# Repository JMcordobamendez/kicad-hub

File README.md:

# kicad-hub

Git-based hardware design review for KiCad, running entirely on GitHub.

The goal is the collaboration experience of commercial PCB cloud platforms
(design checks, BOM review, release packages, web viewer, visual diffs) for KiCad
projects, using only free and open-source tools on top of plain git, GitHub Actions
and GitHub Pages. No extra server to maintain.

kicad-hub is an independent project, not affiliated with or endorsed by the KiCad
project. KiCad is a trademark of its respective owners.

> **Status:** v1.3 — CI checks, BOM review, suppliers, fab package, variants and the
> design portal (compare, comments, nets, cross-probing) work and are tested on every push with a real
> board (see [what works today](#what-works-today)). Next steps: the
> [roadmap](docs/ROADMAP.md).

New here? Read the [manual](docs/manual.md).

| Changed sheet, swipe between before and after | The report posted on the pull request |
|---|---|
|  |  |

More: [schematic](docs/screenshots/portal-schematic.png) ·
[BOM](docs/screenshots/portal-bom.png). Real screenshots of the example board's
portal and PR comment, taken by the "Docs screenshots" workflow.

## What works today

On every push and pull request of a KiCad project, the action:

- **Checks the design**: ERC and DRC (plus schematic/PCB parity) with `kicad-cli`.
  Non-blocking by default; `strict: true` fails the job on errors.
- **Checks the BOM**: every fitted part needs the required fields (by default
  footprint, datasheet and MPN or LCSC code); capacitors need a voltage rating.
- **Checks your requirements**: a `kicad-hub-requirements.yaml` next to the project
  (cost per board, layers, board size, stock, parts...) is checked on every run and
  shown as a pass/fail table; `strict: true` fails the job on a failed requirement.
- **Diffs the BOM** of a pull request against its target branch: parts added,
  removed and changed (`Value: 10uF → 22uF`).
- **Resolves the datasheets**: links checked (broken vs. not checked: a slow or bot-blocking site gets one retry
  and is then listed apart, never as broken), local PDFs
  found by MPN or value in the datasheet folders and bundled for offline use.
- **Prices the BOM from several suppliers**: price and stock of every part at LCSC
  and JLCPCB (no API key needed) and at Mouser, Farnell and DigiKey (with your own
  free API keys); cost per board and per batch (1, 5, 10, 100 boards) for every
  variant; a page to compare offers part by part and choose the supplier, saved in
  the repo. Warns on parts out of stock, not active, not found, or whose LCSC code
  doesn't match the MPN.
- **Builds a fab package** in standard formats any fab house accepts (Gerber X2,
  Excellon, IPC-D-356, BOM and pick & place CSV) with fab notes read from the
  board, which warn about features below the project rules.
- **Reports** all of the above in the job summary and as **one comment on the PR**,
  updated on every push.
- **Builds every design variant** (KiCad 10 variants, read from the project): the
  report lists what each one fits, leaves out or changes, warns when a variant
  changes a value but keeps the part number, diffs each variant in pull requests,
  and the fab package gets a BOM and pick & place per variant. Pick & place follows the
  schematic's per-variant DNP, so the report also compares the schematic with the PCB
  (DNP, excluded-from-BOM / position-files attributes, references, values, and the
  PCB's own per-variant overrides when the board stores them) and shows a "Schematic vs
  PCB" line per build: "in sync" or a table to fix with *Update PCB from Schematic*. The
  fab notes warn when a build's pick & place disagrees with the PCB.
- **Shows before/after images** of the schematic sheets and PCB layers changed in a
  pull request, right in the PR comment: removed in red, added in green, each
  changed area boxed.
- **Publishes a design portal** on GitHub Pages: one page per branch, release and
  pull request with the schematic and PCB in the browser
  ([KiCanvas](https://kicanvas.org)), the report, interactive BOM, supplier
  comparison, datasheets and downloads; the PR comment links to it. Keeps a **timeline**
  of the last commits of `main` and the releases, a page to **compare any two
  versions** (BOM, schematic sheets, PCB layers) and an **activity** page with the
  branch graph, pull requests, reviews, comments and pushes.
- **Publishes a GitHub Release** with the fab package when you tag `vX.Y`.
- Also: schematic PDF, BOM (CSV/HTML) and interactive BOM.

A board still being drawn (no outline on `Edge.Cuts`) skips DRC and the PCB outputs
with a warning instead of failing.

## Planned

Details and progress: [roadmap](docs/ROADMAP.md).

## How the pieces fit together

```
 KiCad (each designer)
        │  git push / pull request / tag
        ▼
 GitHub repository ──► GitHub Actions ── kicad-hub action (Docker: KiCad 10 + KiBot)
                          │
                          ├─ kicad-cli ── ERC / DRC
                          │            ── per-part BOM (this commit + PR base)
                          │            ── SVG of every sheet/layer (this commit + PR base)
                          │            ── fab package: Gerber X2, Excellon,
                          │               IPC-D-356, BOM, pick & place
                          ├─ Python ──── scripts/datasheets.py  resolve, check, bundle
                          │            ── scripts/fabnotes.py    fab notes from the board
                          │            ── scripts/sourcing.py    cost and stock (LCSC, JLCPCB,
                          │                                      Mouser, Farnell, DigiKey)
                          │            ── scripts/visual_diff.py before/after images
                          │            ── scripts/renders.py     page renders for the compare page
                          │            ── scripts/activity.py    branches, PRs, pushes for the activity page
                          │            ── scripts/report.py      markdown report
                          ├─ KiBot ───── schematic PDF, BOM CSV/HTML, iBOM
                          │
                          ├──► job summary + sticky PR comment (images: branch kicad-hub-images)
                          ├──► design portal (branch kicad-hub-site → GitHub Pages)
                          ├──► artifact <board>-fab
                          └──► GitHub Release (on tags)

 GitHub Pages (branch kicad-hub-site): design portal, one page per branch / release / PR
```

`kicad-cli` is used wherever possible: it respects the settings saved in the
project (plot layers, rules) and its options are stable. KiBot is kept for the
outputs it does best.

## Usage

kicad-hub is a GitHub Action. A board repository only needs a small workflow:

```yaml
# .github/workflows/kicad.yml in your board repository
name: KiCad

on:
  push:
    branches: [main]
    tags: ["v*"]         # tagging vX.Y publishes the fab package as a release
  pull_request:

permissions:
  contents: write        # releases and PR images (read = neither)
  pull-requests: write   # PR comment with the report
  issues: read           # issues on the activity page (needed in private repositories)

jobs:
  board:
    runs-on: ubuntu-latest
    steps:
      - uses: actions/checkout@v4
        with:
          lfs: true
      - uses: JMcordobamendez/kicad-hub@v1
        with:
          project-dir: hardware/my-board   # folder with the .kicad_pro
```

Ready-made workflows are in [`template/.github/workflows/`](template/.github/workflows/):
`kicad.yml` (the one above, with every option and the supplier keys) and
`kicad-hub-cleanup.yml`, which removes a pull request's before/after images and its
portal page when it is closed (or by hand, *Run workflow* with a PR number). Copy both to `.github/workflows/` in your board repository.

**Versions:** `@v1` always points to the latest 1.x release (no breaking changes);
pin a full tag such as `@v1.0.0` to freeze it, or use `@main` for the development
version.

### Inputs

| Input | Default | What it does |
|---|---|---|
| `project-dir` | — | Folder with the `.kicad_pro` (required) |
| `strict` | `false` | Fail on ERC/DRC errors or a failed requirement |
| `required-fields` | `Footprint,Datasheet,MPN\|LCSC` | Fields every fitted part needs; `A\|B` = either |
| `check-capacitor-voltage` | `true` | Capacitors need a `Voltage` field or a value like `10uF 16V` |
| `datasheet-dirs` | — | Extra folders with datasheet files (matched by MPN or value) |
| `datasheet-optional-refs` | `R,C,TP,H,MH,FID,JP,NT,LOGO` | Prefixes that don't need a datasheet |
| `check-datasheet-links` | `true` | Check that datasheet URLs respond |
| `variants` | `auto` | Design variants to build: `auto` (all in the project), a list, or `none` |
| `sourcing` | `true` | Price and stock per supplier, and the comparison page |
| `boards` | `1,5,10,100` | Batch sizes to price (components only) |
| `currency` | `USD` | Currency for all prices (converted with ECB rates) |
| `sourcing-choices` | `kicad-hub-sourcing.csv` | Supplier picked per part, relative to `project-dir` (see [choosing suppliers](#choosing-suppliers)) |
| `mouser-api-key` | — | Mouser Search API key, from a secret ([how](#supplier-api-keys)) |
| `farnell-api-key` | — | Farnell / element14 API key, from a secret |
| `farnell-store` | `uk.farnell.com` | Farnell store to price from (`es.farnell.com`, `de.farnell.com`, `www.newark.com`…) |
| `digikey-client-id` | — | DigiKey API client ID, from a secret |
| `digikey-client-secret` | — | DigiKey API client secret, from a secret |
| `requirements` | `kicad-hub-requirements.yaml` | Requirements file, relative to `project-dir` (see [requirements](#requirements)); no file = nothing checked |
| `pages` | `true` | Publish the design portal (see [design portal](#design-portal)) |
| `pages-branch` | `kicad-hub-site` | Branch the portal is published to |
| `history` | `10` | Light snapshots of the last N commits of the default branch for the portal's timeline and compare page; `0` = off |
| `pr-commits` | `20` | Light snapshot of the head commit of every push to a pull request (`/pr-<N>/commits/<sha7>/`), the newest N per PR, to compare a PR's commits with each other; `0` = off |
| `activity` | `500` | Activity page of the portal: graph of the last N commits of all branches, pull requests, reviews, comments, releases and pushes (see [activity](#activity)); `0` = off |
| `visual-diff` | `true` | On PRs, before/after images of the changed sheets and layers in the comment (stored in the `kicad-hub-images` branch) |
| `fab-profile` | `generic` | Optional fab layer: `jlcpcb`, `pcbway` or `eurocircuits` (see [fab profiles](#fab-profiles)) |
| `extra-formats` | — | Extra formats in the fab package: `odb`, `ipc2581` |
| `release` | `true` | On tags, attach the fab package to a GitHub Release |
| `comment` | `true` | Post the report on the PR |
| `github-token` | `github.token` | Token for the PR comment and the release |
| `image` | `ghcr.io/inti-cmnb/kicad10_auto:1.9.1` | Docker image with KiCad and KiBot |
| `output-dir` | `fab` | Where outputs are written |

Outputs: `has-pcb`, `missing-fields`, `requirements-failed`.

Datasheet folders searched by default: `datasheet(s)/` and `docs/` next to the
project, and `datasheet(s)/` one level up. A file is used when its name contains
the part's MPN or value, or its family code (`S-82A2A_B_C.pdf` →
`S-82A2AAA-A8T2U`).

### Fab profiles

The package and the checks are generic by default. `fab-profile` adds an optional
layer for one fab, without changing the project's own DRC or `strict`:

- **DRC vs the fab's rules**: a second DRC on a copy of the project, with the fab's
  published capabilities (`fab-profiles/<name>/rules.kicad_dru`) appended to the
  project's own `.kicad_dru`. Shown as its own line in the report, the PR comment and
  the portal; the artifact has `reports/drc-fab.rpt|json`. It never fails the build.
- **Assembly files** in the fab's column layout, next to the generic ones
  (`assembly/jlcpcb/`: BOM `Comment, Designator, Footprint, LCSC Part #` from the
  `LCSC` field, and CPL `Designator, Mid X, Mid Y, Layer, Rotation`).
- A note in the package's `README.txt`.

| Profile | Rules | Assembly files |
|---|---|---|
| `jlcpcb` | standard 2-layer/multilayer, 1 oz | yes |
| `pcbway` | standard process, 1 oz | no (generic files) |
| `eurocircuits` | only limits independent of the pattern class | no (generic files) |

Each `rules.kicad_dru` cites its source page and date. KiCad rules can't test the
layer count, so where 2-layer and multilayer limits differ the safer value is used.

### Design portal

Every push to a branch, tag and pull request publishes a page to the
`kicad-hub-site` branch, served by GitHub Pages at
`https://<owner>.github.io/<repo>/`:

- `/<branch>/` (e.g. `/main/`), `/releases/<tag>/`, `/pr-<N>/`, and a front page
  listing them all;
- each page has tabs: **Schematic** (sheet picker) and **PCB** (top/bottom, layer
  list with presets), both with pan, zoom and a side panel that shows the clicked
  part (value, footprint, nets, datasheet, best supplier offers); on pull requests,
  **Changes vs <base>** (BOM changes, and each changed sheet or layer in an interactive
  compare: swipe, fade, side by side or red/green changes, with zoom and pan); then **Interactive
  BOM**, **BOM**, **Suppliers**, **Report**, **Datasheets** and **Downloads** (fab
  package, schematic PDF, BOM CSV, commit history);
- **nets in the schematic**: click a wire, bus, junction, label, power symbol or pin and its
  net is highlighted on the sheet (the rest dims) and on the other sheets it runs through,
  with a **Net in the schematic** card (Prev / Next sheet, **Show on PCB**). The viewer builds
  the schematic's connectivity itself (a [fork of KiCanvas](scripts/vendor/README.md));
- **cross-probing**: with a footprint selected, **Show in schematic** opens the sheet that
  has the symbol (a multi-unit part opens on its first unit) and selects it, and **Show on
  PCB** does the reverse (turning the board to the footprint's side); a highlighted net
  has **Show in schematic**, which highlights it sheet by sheet (Prev / Next sheet), and
  the nets of a selected symbol or of a picked wire highlight on the board. An optional
  **Sync** toggle (`?sync=1`) selects the part, or the net, in both tabs;
- a version picker in the top bar jumps between branches, the history of `main`,
  releases and PRs, and opens the timeline or the compare page;
- **History** (front page, `#history`): the last commits of `main` (input `history`,
  default 10, `0` = off) and the releases, newest first, with date, commit, message,
  author, ERC/DRC status, **Open**, **Compare with previous** and **Compare with…**.
  Each push to `main` adds a light snapshot at `/history/<short-sha>/` (design files if
  under 6 MB, page renders, parts BOM, commit info; no fab package, offers or PDFs) and
  the oldest beyond `history` are removed. Releases keep their full pages;
- **Compare** (`/compare.html`, or `compare.html?a=<path>&b=<path>` with paths such as
  `main/`, `history/<sha>/`, `releases/<tag>/`, `pr-3/`): pick any two versions. It shows
  the BOM changes (added, removed, changed fields) and every schematic sheet and PCB layer
  in the interactive compare (swipe, fade, side by side, or **Changes**: red only in A,
  green only in B), computed in the browser from full-page renders that every published
  build stores in `renders/` (same export options and resolution, no crop, so any two
  builds line up). Without parameters it opens on the newest version against the one before
  it (a PR's previous push, else the default branch; for `main` the previous snapshot). Pages identical in both are collapsed as "no changes". Builds
  published before this feature have no renders until their next publish.
- **Commits of a pull request**: every push to a PR also publishes a light snapshot of its
  head commit at `/pr-<N>/commits/<sha7>/` (same content as a `history/` snapshot; input
  `pr-commits`, default the newest 20 per PR, `0` = off; they go away with the PR's page). A PR
  page gets a **Commits** tab: its pushes as a strip (comments counted above each), click one
  for **A** and another for **B** and the two are compared right there (BOM changes and every
  sheet and layer), with a link to the full compare page. The snapshot is the PR merged into its base
  at that push, like the `/pr-<N>/` page, and only the head commit of each push gets one (a push
  of three commits makes one snapshot); a PR pushed before the feature has none until its next push;
- **Activity** (`/activity.html`, linked from the front page and the top bar): how the
  work evolved, with commits, pull requests, comments and issues in one graph, see [below](#activity);
- **Nets and measuring** in the viewer: on the PCB tab, the **Nets** card searches every
  net of the board as you type; the nets of the selected part are buttons too, and a click on
  a track does the same. The net's tracks, vias, pads and zones are highlighted and the
  copper dimmed, with its pad, track (length), via and zone count; **Prev / Next pad**
  centres each pad in turn ("U3 pad 12 · 3 of 18", turning the board over for a pad on the
  other side). **Measure** (PCB and schematic) draws the distance, dx and dy between two
  clicks or taps (on the PCB the points snap to a pad centre when you click near one).
  **Esc** or **Clear** drops the highlight and the measurement. Measure and **Comment** are
  exclusive. The schematic has no net highlight (the viewer doesn't offer one);
- **Design variants** in the viewer: when the design has KiCad variants, the Schematic and
  PCB toolbars get a **Variant** picker (default | each variant), the same in both tabs and
  kept in the URL (`?variant=lite`, so a link opens that variant). The parts not fitted are
  marked: on the PCB a hatched box with a red X and a "DNP" label over each footprint
  (the other side of the board as a faint outline), on the schematic KiCad's own DNP cross
  over the symbol. The toolbar says how many parts the variant leaves out and changes, and
  the **Selected** card shows that variant's values (`C10: 10uF (default: 100nF)`), "Not
  fitted in lite" for a part left out, and its own offers if the variant orders another part;
- on pull request pages, **comments pinned on the board** (see below).

The viewer is a pinned copy of KiCanvas (`scripts/vendor/`, see its README), not
loaded from a third-party site, so published pages don't change under you.

**Turn it on once:** after the first run, *Settings → Pages → Build and deployment →
Source: Deploy from a branch → `kicad-hub-site` / `(root)` → Save*. The PR comment
links to the PR's page. The branch keeps a single commit, replaced on every
publish, so it doesn't grow; the cleanup workflow removes a PR's page when it is
closed. Pull requests from forks aren't published (they can't write to the repo).

**No Pages, no link.** The action asks the GitHub API whether Pages serves the portal
branch. If not (typically a private repository without a paid plan, or Pages not enabled
yet) the PR comment and job summary say so instead of linking to a 404; the portal branch
is still published, so it works as soon as Pages is turned on. If the token can't read the
setting the link is kept as before.

#### Activity

`activity.html` draws the history of the repository: a lane graph of the last commits of
every branch and tag (newest on top, one colour per lane, merge curves, a star on
releases) with what happened between them on the same timeline: pull requests opened,
merged or closed, reviews and review comments, pinned board comments and conversation
comments, issues opened, commented and closed, releases. Next to each commit: subject,
author, date, sha and a green *snapshot* mark when the portal has a page of that exact
commit. A chip at each branch tip shows who created the branch: the author of its pull
request, else of its first commit, else whoever pushed it first. Hover (or focus) an event
to highlight its commits and the reverse. **Show** checkboxes (main, pull requests, PR
commits, comments, issues, releases) and filters (branch, author, dates) narrow it down.

- **Pick two commits to compare**: click a commit (its row or its node) and it becomes **A**,
  click another and it becomes **B**; a third click starts again, and clicking A or B lets it
  go. The bar above the graph shows both, with **Compare A ↔ B** (opens `compare.html` with
  them) and **Clear**. From the keyboard: arrows move between rows, Enter picks, `a` / `b` set
  that slot. Commits without a snapshot are greyed, with a tooltip saying why (only the last
  commits of `main`, the head of each PR push and releases are published): they can still be
  selected to read, not compared. Works for `main`, PR commits and releases alike. A and B are
  kept in the URL (`?a=<sha7>&b=<sha7>`).
- **Side panel** for the selected commit: message, author, date and branch; its pull request
  (title, description, number of commits and snapshots, ERC/DRC of the PR build); the PR's
  review comments (marked *on this commit* when GitHub knows the commit), pinned board comments
  (linking back to the part) and conversation; and the related issues (referenced as `#12`,
  `closes #12` or a link in a commit message or a PR title or description) with their
  description and every comment. Descriptions and comments are GitHub Markdown, sanitised with
  the portal's DOMPurify; pictures are shown as links. **Open this version**, **Set as A / B**,
  **Compare with parent** and **View on GitHub** are at the bottom.
- **Data**: git (all branches and tags in topological order; a shallow checkout is
  deepened and all branches are fetched, so the graph is complete without
  `fetch-depth: 0`) and the GitHub GraphQL API with the action's `github-token` (the last
  100 pull requests with reviews, review comments and comments, the releases, and up to 40
  issues the commits and PRs mention, one query per ten: well inside the rate limit, and skipped
  when little is left). The page itself (`activity.json`) stays light: texts of the selected commit
  are in `activity-details.json`, fetched on the first click (capped at about 2.5 MB: long
  texts are cut). In a **private** repository the token needs `issues: read` (add it to the
  workflow's `permissions`); without it the page says the issues are missing and shows the rest.
  Without the token or when GitHub doesn't answer, the page shows the git graph alone.
- **Pushes**: GitHub doesn't keep who pushed a branch, so every run of a push (and every
  update of a pull request's branch) appends `{actor, ref, before, after, date}` to
  `activity-pushes.json` in the site branch (the last 1000). Pushes made before the first
  run with this feature are not known; the page says since when it records.
- **Privacy**: no e-mail address is ever published. Authors are shown by GitHub login (and
  avatar from `avatars.githubusercontent.com`) when known, else by the name in the commit,
  and anything that looks like an address is removed from commit messages and comments
  (`Co-authored-by` and `Signed-off-by` lines are dropped). Issue and PR texts are published
  to the repository's own Pages site, so they are as public as that site.
- Input `activity` sets how many commits to read (default 500, `0` = no page). Pull requests
  from forks aren't published, so they never reach it.

#### Comments on the board

On a pull request's page, the **PCB** and **Schematic** tabs have a **Comment** button.
Press it, click a part or any point of the board (or type the coordinates), write the
note and post it: it becomes a normal comment in the pull request's conversation,

```
📍 **U12** (x 23.40, y 41.10 mm, F.Cu) — missing decoupling

[Open on the board](https://<owner>.github.io/<repo>/pr-7/?at=23.4,41.1&ref=U12#pcb)
<!-- kicad-hub-pin {"ref":"U12","x":23.4,"y":41.1,"layer":"F.Cu","page":"pcb","sha":"…"} -->
```

with a hidden marker that the portal reads back. The **Comments** card in the side
panel lists the pins of that tab (author, part, text, link to the GitHub comment);
click one to select and zoom to the part (or the point), and numbered markers are
drawn over the viewer and follow pan and zoom. The link in the comment opens the page
on that spot. Anyone can also write such a comment by hand: the marker is all it needs.
Branch and release pages don't show comments.

Reading the pins needs nothing (public repositories, 60 anonymous requests per hour).
**Posting** from the page needs a token; without one, **Comment** copies the formatted
comment to the clipboard and opens the pull request, where you paste it.

*Make the token once* (GitHub, in the browser):

1. Click your profile photo, top right → **Settings**.
2. Left sidebar, at the bottom → **Developer settings**.
3. **Personal access tokens** → **Fine-grained tokens** → **Generate new token**.
4. **Token name**: `kicad-hub comments`. **Expiration**: 30 days is plenty.
5. **Resource owner**: the owner of the board repository (an organization may need to
   allow fine-grained tokens, or approve the request).
6. **Repository access** → **Only select repositories** → pick the board repository.
7. **Permissions** → **Repository permissions** → **Pull requests** → *Access:*
   **Read and write** (Metadata: Read-only is added by itself). Nothing else.
8. **Generate token**, copy it (`github_pat_…`) and paste it in the **GitHub token**
   box at the bottom of the Comments card → **Save**.

The token is kept in this browser's `localStorage` and sent only to `api.github.com`,
never in a URL or to any other site. **Forget token** (same box) removes it. Comments
are posted under your GitHub account. `localStorage` is shared by every page under
`<owner>.github.io`, so keep the expiry short and the permission to that one
repository.

### Supplier API keys

LCSC and JLCPCB work out of the box: parts are looked up by their `LCSC` field
(e.g. `C25744`), no account needed. Mouser, Farnell and DigiKey need an API key,
which each user gets for free with their own account — kicad-hub has no shared
keys. Parts are looked up there by their `MPN` field, or by the manufacturer part
number LCSC reports when the MPN is empty. Add only the suppliers you want; the
others are skipped and listed as "no API key" in the report.

**1. Get the keys**

- **Mouser** — sign in at [mouser.com](https://www.mouser.com) (create an account if
  needed), open the [API Hub](https://www.mouser.com/api-hub/) and sign up for the
  **Search API**. The key is shown under *My Account → APIs* and sent by email.
  Limits: 30 requests per minute, 1,000 per day (one request per part).
- **Farnell / element14** — register at
  [partner.element14.com](https://partner.element14.com/), then *Register an
  application* / *Get API Keys* for the **Product Search API (REST)**. Copy the key.
  Pick your store with `farnell-store` (prices come in that store's currency).
- **DigiKey** — sign in at [developer.digikey.com](https://developer.digikey.com/)
  with a DigiKey account, create an organization, then a **Production App** with
  the **ProductInformation V4** API enabled (the OAuth callback can be
  `https://localhost`, it isn't used). Copy its **Client ID** and **Client Secret**.

**2. Store them as secrets of your board repository** (never in a file): *Settings →
Secrets and variables → Actions → New repository secret*, one per value:

| Secret name | Value |
|---|---|
| `MOUSER_API_KEY` | Mouser Search API key |
| `FARNELL_API_KEY` | element14 API key |
| `DIGIKEY_CLIENT_ID` | DigiKey Client ID |
| `DIGIKEY_CLIENT_SECRET` | DigiKey Client Secret |

**3. Pass them to the action** in your workflow:

```yaml
      - uses: JMcordobamendez/kicad-hub@v1
        with:
          project-dir: hardware/my-board
          currency: EUR
          mouser-api-key: ${{ secrets.MOUSER_API_KEY }}
          farnell-api-key: ${{ secrets.FARNELL_API_KEY }}
          farnell-store: es.farnell.com
          digikey-client-id: ${{ secrets.DIGIKEY_CLIENT_ID }}
          digikey-client-secret: ${{ secrets.DIGIKEY_CLIENT_SECRET }}
```

A secret that isn't set arrives empty and that supplier is skipped, so the same
workflow works with any subset. GitHub masks secrets in the logs. Pull requests
from forks don't get secrets: they are priced with LCSC and JLCPCB only.

### Choosing suppliers

By default each part is bought from the cheapest supplier that has enough stock for
the batch. To choose yourself:

1. Download the artifact of a run and open **`sourcing.html`**: one row per part,
   with every supplier's stock, minimum order, unit price and line total for the
   batch you select, and totals per build and batch.
2. Pick an offer per part (or *Use the cheapest for every part* to freeze the
   current choice). **Download purchase list** gives one CSV per batch, sorted by
   supplier, ready to paste into each supplier's cart.
3. **Download selection file** and commit it as `kicad-hub-sourcing.csv` next to
   the `.kicad_pro`. From then on the report's totals use your picks; parts not in
   the file stay automatic. It's a plain CSV (`Part,Supplier,SKU`, where `Part` is
   the MPN or the LCSC code), so it can also be edited by hand and reviewed in PRs.

**Target price.** An optional fourth column, `Target`, is the unit price you want to
pay for a part, in the `currency` input (`Part,Supplier,SKU,Target`). A row may carry
only `Part` and `Target`, leaving `Supplier` and `SKU` empty: no choice, just a
target. Files without the column keep working. In `sourcing.html` type the target
next to a part; offers above it turn red, and **Download selection file** writes
the column. The report's *Cost and stock* section then lists an **Above target
price** table (part, references, target, unit price of the offer used at the
largest batch, supplier, percentage over) and `above_target` is added to the
counts; `reports/sourcing.csv` has a `Target` column and a `Vs target @n` column per
batch, and `sourcing.json` a `vs_target` entry per part (`above`, `ok` or `no offer`).
The example board has a [`kicad-hub-sourcing.csv`](examples/royalblue54l-feather/kicad-hub-sourcing.csv)
with a few targets, one of them set too low on purpose so the warning shows.
A `Target price` symbol field is not read: the BOM export only carries the fields
listed in `required-fields`-style columns, so targets live in the CSV.

### Requirements

Write down what the board has to meet and let CI check it. Put a
`kicad-hub-requirements.yaml` next to the `.kicad_pro` (the `requirements` input
renames it); without the file nothing is checked and nothing is shown. Each entry
has an `id`, a human `text`, a `check` type and that check's parameters:

```yaml
- id: R1
  text: Cost per board under 15 EUR at 100 units
  check: max_cost
  batch: 100
  max: 15
```

The report gets a **Requirements** table (id, requirement, result, measured value) and
the portal's Checks panel counts the failed ones. A requirement is **pass**, **fail**,
or **unknown** when the data to check it isn't there (no prices, no board outline, a
batch that isn't priced): unknown never fails the job. A malformed entry (unknown check,
missing or misspelled parameter, duplicate id, invalid regex) is reported as **fail**
with the reason. Failed requirements fail the job only with `strict: true`. The file
is read with PyYAML inside the KiBot image; a top-level `requirements:` list is also
accepted. A commented template is in [`template/`](template/kicad-hub-requirements.yaml)
and a working one in [`examples/royalblue54l-feather/`](examples/royalblue54l-feather/kicad-hub-requirements.yaml).

| `check` | Parameters | Passes when |
|---|---|---|
| `erc_errors_max` | `max` (default 0), `severity` (`error`, or `warning`) | ERC violations of that severity ≤ `max` |
| `drc_errors_max` | `max` (default 0), `severity` | DRC violations ≤ `max` (unknown without a board outline) |
| `max_parts` | `max`, `variant` | Fitted parts (DNP excluded) ≤ `max` |
| `max_unique_parts` | `max`, `variant` | Distinct fitted parts ≤ `max` (same MPN or LCSC code, else same value and footprint, counts once) |
| `max_cost` | `max`, `batch`, `variant` | Components cost per board at `batch` boards ≤ `max`, in the `currency` input. `batch` must be in the `boards` input. Unknown if some parts have no price and the priced ones are still within `max` |
| `in_stock` | `batch`, `variant` | Every part has a supplier with stock for `batch` boards (the picked supplier if `kicad-hub-sourcing.csv` chooses one) |
| `max_above_target` | `max` (default 0), `batch` (default: largest in `boards`), `variant` | Parts whose used offer costs more than their `Target` in `kicad-hub-sourcing.csv` ≤ `max`. Unknown without any target |
| `no_bad_lifecycle` | `variant` | No part is obsolete / EOL / NRND at every supplier that reports its lifecycle |
| `max_layers` | `max` | Copper layers ≤ `max` |
| `max_board_size` | `width`, `height` (mm) | Board outline fits in `width` x `height`, either orientation |
| `min_track` | `min` (mm) | Narrowest track used ≥ `min` |
| `min_drill` | `min` (mm) | Smallest drill used (vias and plated pad holes) ≥ `min` |
| `required_fields` | `refs`, `fields`, `variant` | Every fitted part whose reference matches the regex `refs` (whole reference, e.g. `U\d+`) has all `fields` filled. Fields are the exported BOM columns (see `required-fields`) |
| `variants_in_sync` | `max` (default 0), `variant` | Differences between the schematic and the PCB (DNP, attributes, missing references, values) ≤ `max`, for every build or only `variant` |
| `forbidden_parts` | `pattern`, `variant` | No fitted part has an MPN or value matching the regex `pattern` (case-insensitive) |

`variant` is the name of a design variant; leave it out for the default build.
`max_cost`, `in_stock`, `max_above_target` and `no_bad_lifecycle` need `sourcing: true`.

### What you get

**Report** — job summary and PR comment:
ERC/DRC counts · requirements pass/fail · BOM changes vs. the PR base · before/after images · variants · parts missing required fields ·
datasheet status (broken links, offline copies) · cost per batch and stock warnings ·
fab package warnings.

**Artifact `<board>-fab`:**

```
reports/      erc/drc (.rpt, .json), per-part BOMs, report.md, datasheets.json,
              sourcing.csv (every supplier offer per part and batch)
sourcing.html supplier comparison: choose per part, download selection and purchase list
package/      <board>-<rev>-fab.zip  ← send this to the fab
  <board>-<rev>/
    gerber/       Gerber X2 + .gbrjob (layers as set in the board's plot settings)
    drill/        Excellon PTH and NPTH, drill maps (PDF)
    assembly/     BOM (CSV, grouped, no DNP) and pick & place (CSV, mm, both sides)
      <variant>/  the same for each design variant
      <fab>/      with a fab-profile: BOM and pick & place in that fab's columns
    *.d356        IPC-D-356 netlist for electrical test
    README.txt    fab notes: size, layers, stackup, finish, smallest features, warnings
    SHA256SUMS.txt
visual/       PRs only: before/after (<page>.png) and full-page overlay (<page>-full.png)
datasheets/   local datasheets + index.html (part → datasheet)
schematic/    schematic PDF
bom/          BOM CSV and HTML (KiBot)
ibom/         interactive BOM
```

The package revision is the tag on releases, else the title block revision, else
the commit hash.

## Repository layout

```
action.yml                  the action
fab-profiles/               optional per-fab DRC rules and assembly column layouts
scripts/                    fab_assembly.py, report.py, requirements.py, datasheets.py, fabnotes.py,
                            variant_cpl.py, variant_sync.py, visual_diff.py, renders.py (page renders for the
                            compare page), sourcing.py (+ sourcing.html, the comparison page),
                            portal.py (+ portal.html, the design portal; compare.html and
                            compare.js, the compare page and its shared widget;
                            pins.js, comments pinned on the board;
                            viewer-tools.js, nets and measuring;
                            variants-view.js, variant picker and DNP marks; activity.py +
                            activity.html, the activity page)
kibot/default.kibot.yaml    KiBot outputs (schematic PDF, BOMs, iBOM)
template/                   starting point for a new board repository
examples/                   boards used to test the action (see examples/README.md)
.github/workflows/test.yml  runs the action on the example board on every push/PR/tag
.github/workflows/kicad-hub-cleanup.yml  removes closed PRs' images and pages (same as the template's)
docs/                       roadmap and screenshots
```

New board repositories start from [`template/`](template/): folder layout,
`.gitignore`, `.gitattributes` (LF for KiCad files, Git LFS for 3D models),
project libraries through `${KIPRJMOD}`, a PR design review checklist and the CI
workflows.

### Approval flows

The template includes issue forms (part request, design review, fab release), a
`CODEOWNERS.example` and an opt-in approval step for releases, all plain GitHub
features. Step-by-step recipes: [`template/docs/approvals.md`](template/docs/approvals.md).

## Development

- Every push to `main`, every PR and every `v*` tag runs the action on
  `examples/royalblue54l-feather` (`.github/workflows/test.yml`). A PR shows the
  report comment. Version tags (`v*`) run the tests only; an `example-*` tag also
  publishes the example's fab package as a release, to test that step.
- The Python scripts can be run locally against files exported with a local
  `kicad-cli` (see the arguments at the top of each script). `fabnotes.py` needs
  KiCad's own Python (`pcbnew`); on Windows it may open a "font not found" dialog
  that blocks until closed — that doesn't happen in CI.

## Report notes

- **BOM changes** list the fields of a changed part by importance (Value, Footprint,
  MPN/Manufacturer, supplier codes, the rest). Datasheet URL changes are not in the row,
  only "datasheet link changed", with the before/after in a collapsed list.
- **Lifecycle** (obsolete, NRND, EOL…) is a status of one supplier's orderable part. It is a
  warning only when it hits an offer the totals use or several suppliers report it;
  otherwise it is a note in `sourcing.html`.
- If the workflow calls the action at a branch (`@main`) the report says it is a
  development branch; pin `@v1` for the stable version. No note for tags or commit SHAs.

## Known limits

- **No real-time co-editing.** KiCad files don't merge well: split work by
  hierarchical sheet and keep a single owner for the PCB at a time.
- **GitHub Pages is free only for public repositories** (private ones need a paid
  plan); without Pages the portal branch is still published but not served.
- The viewer is KiCanvas, still in alpha: some KiCad features may not display.
- PR commit snapshots are of the head commit of each push (not every commit of a push), are
  the PR merged into its base at that moment (so they include whatever the base had then), and
  cost the size of a light snapshot each: 20 per open PR is the default, lower `pr-commits` for
  big boards.
- Pinned comments are a prototype (phase 5): conversation comments only (no replies or
  resolving from the page, no review comments on the diff), a pin keeps the position
  where it was made even if the part moves in a later commit, and the viewer's clicks
  rely on KiCanvas internals. Only on pull request pages of github.com repositories.

## License

[MIT](LICENSE). The example board keeps its own license (CERN-OHL-P, see
[examples/README.md](examples/README.md)).

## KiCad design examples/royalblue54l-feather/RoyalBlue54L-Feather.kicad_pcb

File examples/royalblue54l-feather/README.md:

# RoyalBlue54L Feather

An ARM + RISC-V Feather board with the new nRF54L15, built-in debugger, and smart PMIC

## Overview

The RoyalBlue54L--familiar Feather formfactor with distinctive features. Nordic's next-gen nRF54L15, an onboard CMSIS-DAP debugger + UART bridge, and smart power-management features from the nPM1300 enable rapid development for your next Bluetooth 6.0, Thread, Matter, Zigbee, Amazon Sidewalk, or proprietary wireless project.

Crowd Supply project link: https://www.crowdsupply.com/lords-boards/royalblue54l-feather

## Hardware Features

* Dual-core processing power:
  * ARM Cortex-M33 at 128MHz
  * RISC-V co-processor at 128MHz
* Comprehensive memory configuration:
  * 1.5MB of non-volatile memory (NVM)
  * 256KB of RAM
  * 2MB external flash
* Advanced wireless capabilities:
  * BLE 6.0 support with channel sounding for distance estimation
  * 4Mbps PHY for proprietary wireless protocols
  * 30-50% power reduction compared to nRF52 series
* Integrated development tools:
  * CMSIS-DAP debugger (nRF52833-based)
  * USB-to-UART bridge
  * Open source, Zephyr RTOS-based firmware
* Smart power management:
  * USB-C charging up to 800mA with nPM1300
  * High-accuracy battery fuel gauge
* Connectivity:
  * JST-PH connector
  * STEMMA-QT/Qwiic port
  * NFC antenna connector
* User interfaces:
  * User LED
  * RGB LED (nPM1300-driven)
  * User button
  * Reset button

## Project Contents

This project contains the hardware design files for the RoyalBlue54L Feather. The board is designed with KiCAD and includes:

* Schematic files
* PCB layout
* Bill of Materials (BOM)
* Documentation

## Related Repositories

* [Zephyr Board Support](https://github.com/LordsBoards/RoyalBlue-nRF54L15-Zephyr-Boards)
* [Debugger Firmware](https://github.com/LordsBoards/RoyalBlue-nRF54L15-Debugger-Firmware)

## License

Hardware files are released under CERN-OHL-V2-P.

## Modification Note

Modified by KiCad Project Feb 17, 2025
 - Removed Manufacturing files
 - Update README.md

## kicad-hub

`kicad-hub-sourcing.csv` sets target unit prices (USD) for four parts (`Part,Supplier,SKU,Target`, no supplier chosen). `C307331` has a target set far below its real price on purpose, so the report shows an "Above target price" table.

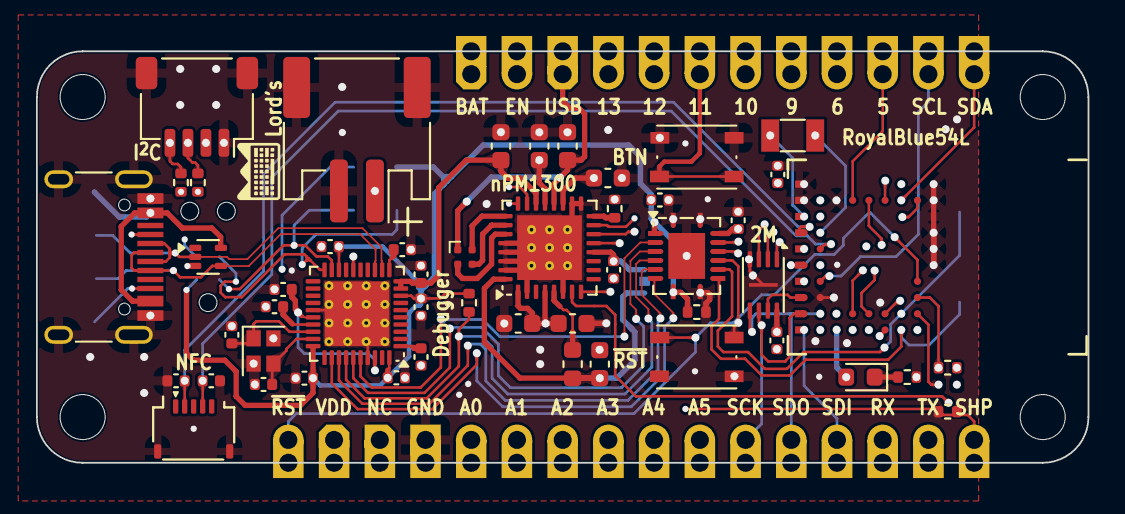
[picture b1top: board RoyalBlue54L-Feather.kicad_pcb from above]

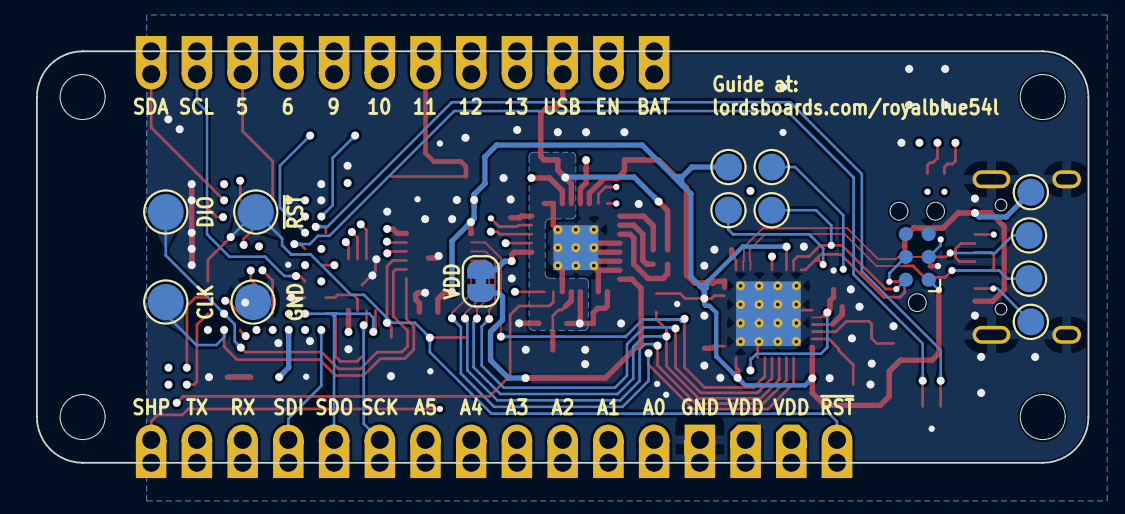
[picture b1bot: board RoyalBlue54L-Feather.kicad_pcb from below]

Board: 8 copper layers, 58.4 x 22.9 mm, 71 parts (15 on the bottom side), 68 nets.

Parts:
C1, C12, C16, C17, C19, C24, C25: 100nF; C_0402_1005Metric
C2, C3, C4, C8: 10uF; C_0603_1608Metric
C5, C6: 1uF; C_0603_1608Metric
C7, C9, C10, C23: 4.7uF; C_0402_1005Metric
C11: 2.2uF; C_0603_1608Metric
C13, C14: 300pF; C_0402_1005Metric
C15, C22: 1uF; C_0402_1005Metric
C18, C20: 12pF; C_0402_1005Metric
C21: 100pF; C_0402_1005Metric
D1: LED_Small; LED_0603_1608Metric
D3: LED_ARGB; LED_Wurth_150044M155260
H1, H2, H3, H4: MountingHole; MountingHole_2.5mm
J1: Conn_01x16_Pin; PinHeader_1x16_P2.54mm_Vertical
J2: Conn_01x12_Pin; PinHeader_1x12_P2.54mm_Vertical
J3: USB_C_Receptacle_USB2.0_16P; USB_C_Receptacle_HRO_TYPE-C-31-M-12
J4: Conn_01x02_MountingPin; JST_PH_S2B-PH-SM4-TB_1x02-1MP_P2.00mm_Horizontal
J5: Conn_01x04_MountingPin; JST_SH_SM04B-SRSS-TB_1x04-1MP_P1.00mm_Horizontal
J6: Conn_01x05_MountingPin; CONN-SMD_5P-P0.50_HCTL_HC-FPC-05-09-5RLTAG
J8: Conn_ARM_SWD_TagConnect_TC2030-NL; Tag-Connect_TC2030-IDC-NL_2x03_P1.27mm_Vertical
JP1: SolderJumper_2_Bridged; SolderJumper-2_P1.3mm_Bridged_RoundedPad1.0x1.5mm
L1: 2.2uH; L_0603_1608Metric
LOGO1: LordsBoardsLogo_Small_Silk
R1, R8: 100kR; R_0402_1005Metric
R2, R3, R7: 10kR; R_0402_1005Metric
R4: 330kR; R_0402_1005Metric
R5: 4.7kR; R_0402_1005Metric
R6: 470R; R_0402_1005Metric
SW1, SW2: SW_Push; SW_Push_1P1T_NO_Vertical_Wuerth_434133025816
TP1, TP2, TP3, TP4: TestPoint; TestPoint_Pad_D2.0mm
TP5, TP6, TP7, TP8, TP9, TP10, TP11, TP12: TestPoint; TestPoint_Pad_D1.5mm
U1: BM15x; BM15x-LGA-45_15.8x10mm
U2: nPM1300-QEXX; QFN-32-1EP_5x5mm_P0.5mm_EP3.6x3.6mm_ThermalVias
U3: TPD3E001DRLR; SOT-553
U4: W25Q16JVUXIQ; Winbond_USON-8-1EP_3x2mm_P0.5mm_EP0.2x1.6mm
U5: nRF52833-QDXX; QFN-40-1EP_5x5mm_P0.4mm_EP3.6x3.6mm_ThermalVias
U6: TXB0106RGY; Texas_RGY_R-PVQFN-N16_EP2.05x2.55mm
Y1: 32.768KHz; Crystal_SMD_3215-2Pin_3.2x1.5mm
Y2: 32MHz; Crystal_SMD_2016-4Pin_2.0x1.6mm

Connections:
+BATT: C11.1, J2.1, J4.1, U2.19 (VBAT)
/Connectors/ANALOG.A0: J1.5, U1.E9 (P1.04/AIN0)
/Connectors/ANALOG.A1: J1.6, U1.F8 (P1.05/AIN1)
/Connectors/ANALOG.A2: J1.7, U1.F9 (P1.06/AIN2)
/Connectors/ANALOG.A3: J1.8, U1.G9 (P1.07/AIN3)
/Connectors/ANALOG.A4: J1.9, U1.B4 (P1.12/AIN5)
/Connectors/ANALOG.A5: J1.10, U1.B5 (P1.13/AIN6)
/Connectors/DIG.D5: J2.10, U1.B6 (P1.14/AIN7)
/Connectors/DIG.D6: J2.9, U1.K4 (P0.01)
/Connectors/DIG.D9: J2.8, U1.K5 (P2.10)
/Connectors/DIG.D10: J2.7, U1.K6 (P2.08)
/Connectors/DIG.D11: J2.6, SW2.1, U1.J4 (P0.00)
/Connectors/DIG.D12: J2.5, U1.J5 (P2.09)
/Connectors/DIG.D13: J2.4, U1.J6 (P2.07)
/Connectors/ENABLE: J2.2, U2.8 (GPIO1)
/Connectors/I2C.SCL: J2.11, J5.4, R2.2, U1.G8 (P1.08)
/Connectors/I2C.SDA: J2.12, J5.3, R3.2, U1.B3 (P1.11/AIN4)
/Connectors/SHPHLD: J1.16, U2.15 (SHPHLD)
/Connectors/SPI.MISO: J1.13, U1.K9 (P2.04), U4.2 (DO/IO_{1})
/Connectors/SPI.MOSI: J1.12, U1.J8 (P2.02), U4.5 (DI/IO_{0})
/Connectors/SPI.SCK: J1.11, U1.J9 (P2.01), U4.6 (CLK)
/Connectors/UART.RX: J1.14, U1.A3 (P1.09), U6.14 (B2)
/Connectors/UART.TX: J1.15, U1.B2 (P1.10), U6.13 (B3)
/Debugger/D+: J3.A6 (D+), J3.B6 (D+), TP7.1, U3.4 (IO3), U5.13 (D+)
/Debugger/D-: J3.A7 (D-), J3.B7 (D-), TP8.1, U3.2 (IO2), U5.12 (D-)
/Debugger/SWD_TRG.SWDCLK: TP3.1, U1.K3 (SWDCLK), U6.10 (B6)
/Debugger/SWD_TRG.SWDIO: TP1.1, U1.J3 (SWDIO), U6.11 (B5)
/Debugger/SWD_TRG.~RESET: J1.1, SW1.2, TP2.1, U1.G2 (~RESET), U6.12 (B4)
/Debugger/TRG_SWDCLK_NRF52: U5.32 (P0.02/AIN0), U6.7 (A6)
/Debugger/TRG_SWDIO_NRF52: U5.33 (P0.28/AIN4), U6.6 (A5)
/Debugger/TRG_~RESET_NRF52: R8.2, U5.34 (P0.29/AIN5), U6.5 (A4)
/Debugger/UART_RX_NRF52: U5.36 (P0.31/AIN7), U6.3 (A2)
/Debugger/UART_TX_NRF52: U5.35 (P0.30/AIN6), U6.4 (A3)
/Debugger/USB.CC1: J3.A5 (CC1), U2.23 (CC1)
/Debugger/USB.CC2: J3.B5 (CC2), TP6.1, U2.24 (CC2)
/Debugger/USB.VBUS: C5.1, J3.A4 (VBUS), J3.A9 (VBUS), J3.B4 (VBUS), J3.B9 (VBUS), TP5.1, U2.21 (VBUS), U3.5
/Debugger/nRF52_VDD: C10.1, C15.1, C16.1, C17.1, C25.1, J8.1 (VCC), R1.1, R8.1, TP9.1, U5.8 (VDD), U5.18 (VDD), U5.30 (VDD), U5.40 (VDD), U6.2 (V_{CCA}), U6.8 (OE)
/nPM1300/NPM1300.INT: U1.K2 (P0.02), U2.7 (GPIO0)
/nPM1300/NPM1300.SCL: R5.2, U1.J2 (P0.03), U2.14 (SCL)
/nPM1300/NPM1300.SDA: R7.2, U1.H2 (P0.04), U2.13 (SDA)
/nRF54L15/D2_FLASH: U1.J7 (P2.03), U4.3 (~WP/IO_{2})
/nRF54L15/D3_FLASH: U1.H9 (P2.00), U4.7 (~HOLD/~RESET/IO_{3})
/nRF54L15/~CS_FLASH: U1.K8 (P2.05), U4.1 (~CS)
GND: C1.2, C2.2, C3.2, C4.2, C5.2, C6.2, C7.2, C8.2, C9.2, C10.2, C11.2, C12.2, C13.2, C14.2, C15.2, C16.2, C17.2, C18.1, C19.2, C20.1, C21.2, C22.2, C23.2, C24.2, C25.2, J1.4, J3.A1 (GND), J3.A12 (GND), J3.B1 (GND), J3.B12 (GND), J3.S1 (SHIELD), J4.2, J4.MP (MountPin), J5.1, J5.MP (MountPin), J6.MP (MountPin), J8.5 (GND), R1.2, R4.2, R6.2, SW1.1, SW2.2, TP4.1, U1.A1 (GND), U1.A9 (GND), U1.B1 (GND), U1.B7 (GND), U1.B9 (GND), U1.D1 (GND), U1.E1 (GND), U1.F1 (GND), U1.H8 (GND), U2.2 (PVSS1), U2.6 (PVSS2), U2.17 (VSET1), U2.18 (NTC), U2.28 (LSIN1/VINLDO1), U2.29 (LSOUT1/VOUTLDO1), U2.30 (LSIN2/VINLDO2), U2.31 (LSOUT2/VOUTLDO2), U2.33 (AVSS), U3.3, U4.4 (GND), U4.9 (EP), U5.25 (VSS_PA), U5.37 (VSS), U5.41 (VSS), U6.1 (A1), U6.9 (GND), U6.16 (B1), U6.17 (GND), Y2.2, Y2.4
unnamed: D1.2 (A), U1.K7 (P2.06)
unnamed: D1.1 (K), R6.1
unnamed: D3.4 (BK), U2.27 (LED2)
unnamed: D3.3 (GK), U2.26 (LED1)
unnamed: D3.2 (RK), U2.25 (LED0)
unnamed: C14.1, J6.2, U1.D9 (P1.02/NFC1)
unnamed: C13.1, J6.4, U1.E8 (P1.03/NFC2)
unnamed: J8.4 (SWCLK), TP11.1, U5.20 (SWDCLK)
unnamed: J8.2 (SWDIO), TP12.1, U5.19 (SWDIO)
unnamed: J8.3 (~RESET), TP10.1, U5.16 (P0.18/~RESET)
unnamed: C8.1, JP1.1 (A), L1.1, U2.32 (VOUT2)
unnamed: U1.D8 (P1.00/XL1), Y1.2
unnamed: U1.C9 (P1.01/XL2), Y1.1
unnamed: L1.2, U2.5 (SW2)
unnamed: R4.1, U2.16 (VSET2)
unnamed: C19.1, U5.1 (DEC1)
unnamed: C21.1, U5.27 (DEC3)
unnamed: C22.1, U5.26 (DEC6), U5.38 (DEC4)
unnamed: C23.1, U5.11 (DECUSB)
unnamed: C18.2, U5.28 (XC1), Y2.1
unnamed: C20.2, U5.29 (XC2), Y2.3
VBUS: C6.1, C7.1, U2.22 (VBUSOUT), U5.9 (VDDH), U5.10 (VBUS)
VDD: C1.1, C9.1, C12.1, C24.1, J1.2, J5.2, JP1.2 (B), R2.1, R3.1, R5.1, R7.1, U1.B8 (VDD), U1.C8 (VDD), U2.12 (VDDIO), U4.8 (VCC), U6.15 (V_{CCB})
VSYS: C2.1, C3.1, C4.1, D3.1 (A), J2.3, U2.1 (VOUT1), U2.4 (PVDD), U2.20 (VSYS)
